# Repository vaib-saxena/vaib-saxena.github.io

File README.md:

## Welcome to my website "vaibsite.com"

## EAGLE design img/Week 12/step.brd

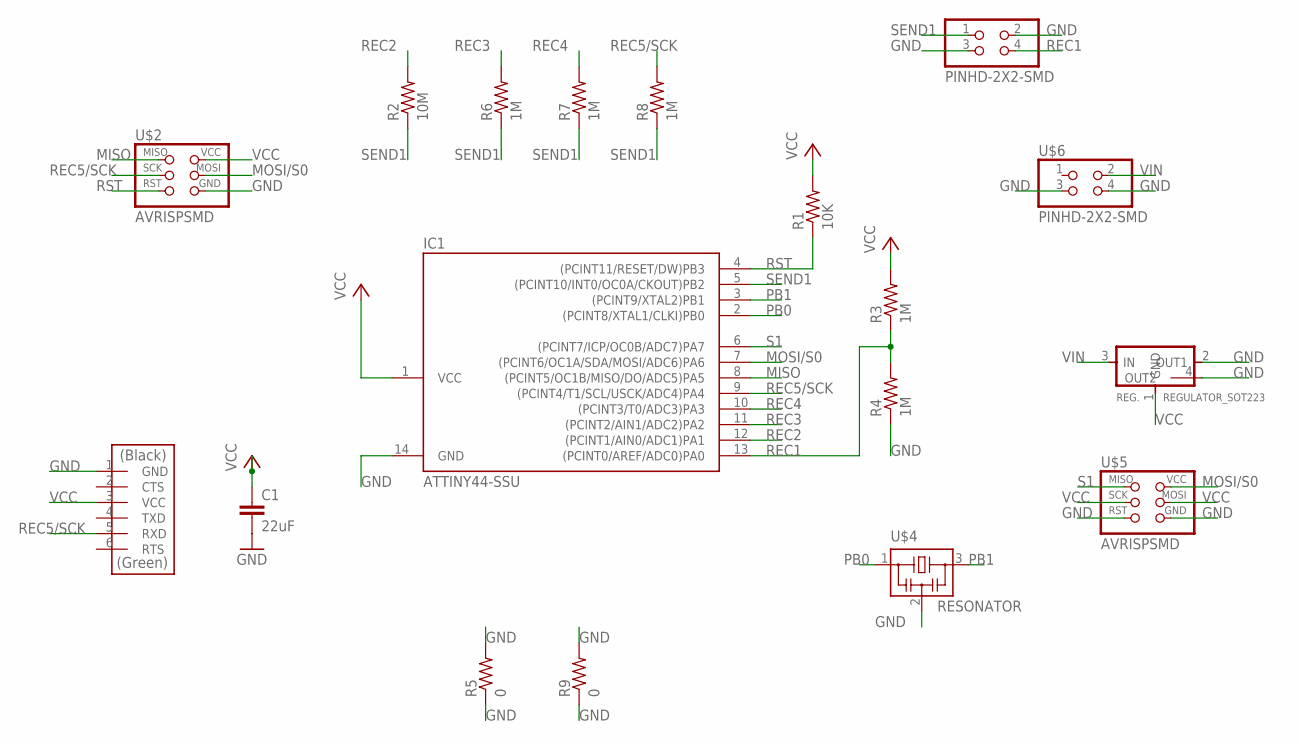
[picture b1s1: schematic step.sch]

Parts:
C1: 22uF; C1206
IC1: ATTINY44-SSU; SOIC14
R1: 10K; R1206FAB
R2: 10M; R1206FAB
R3, R4, R6, R7, R8: 1M; R1206FAB
R5, R9: 0; R1206FAB
REG.: REGULATOR_SOT223; SOT223
STEP/GND-SMD: PINHD-2X2-SMD; 2X02SMD
U$1: FTDI-SMD-HEADER; 1X06SMD
U$2, U$5: AVRISPSMD; 2X03SMD
U$4: RESONATOR; EFOBM
U$6: PINHD-2X2-SMD; 2X02SMD

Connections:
GND: C1.2, IC1.14 (GND), R4.1, R5.1, R5.2, R9.1, R9.2, REG..2 (OUT1), REG..4 (OUT2), STEP/GND-SMD.2, STEP/GND-SMD.3, U$1.1 (GND), U$2.6 (GND), U$4.2, U$5.5 (RST), U$5.6 (GND), U$6.3, U$6.4
MISO: IC1.8 ((PCINT5/OC1B/MISO/DO/ADC5)PA5), U$2.1 (MISO)
MOSI/S0: IC1.7 ((PCINT6/OC1A/SDA/MOSI/ADC6)PA6), U$2.4 (MOSI), U$5.2 (VCC)
PB0: IC1.2 ((PCINT8/XTAL1/CLKI)PB0), U$4.1
PB1: IC1.3 ((PCINT9/XTAL2)PB1), U$4.3
REC1: IC1.13 ((PCINT0/AREF/ADC0)PA0), R3.1, R4.2, STEP/GND-SMD.4
REC2: IC1.12 ((PCINT1/AIN0/ADC1)PA1), R2.2
REC3: IC1.11 ((PCINT2/AIN1/ADC2)PA2), R6.2
REC4: IC1.10 ((PCINT3/T0/ADC3)PA3), R7.2
REC5/SCK: IC1.9 ((PCINT4/T1/SCL/USCK/ADC4)PA4), R8.2, U$1.5 (RXD), U$2.3 (SCK)
RST: IC1.4 ((PCINT11/RESET/DW)PB3), R1.1, U$2.5 (RST)
S1: IC1.6 ((PCINT7/ICP/OC0B/ADC7)PA7), U$5.1 (MISO)
SEND1: IC1.5 ((PCINT10/INT0/OC0A/CKOUT)PB2), R2.1, R6.1, R7.1, R8.1, STEP/GND-SMD.1
VCC: C1.1, IC1.1 (VCC), R1.2, R3.2, REG..1 (GND), U$1.3 (VCC), U$2.2 (VCC), U$5.3 (SCK), U$5.4 (MOSI)
VIN: REG..3 (IN), U$6.2

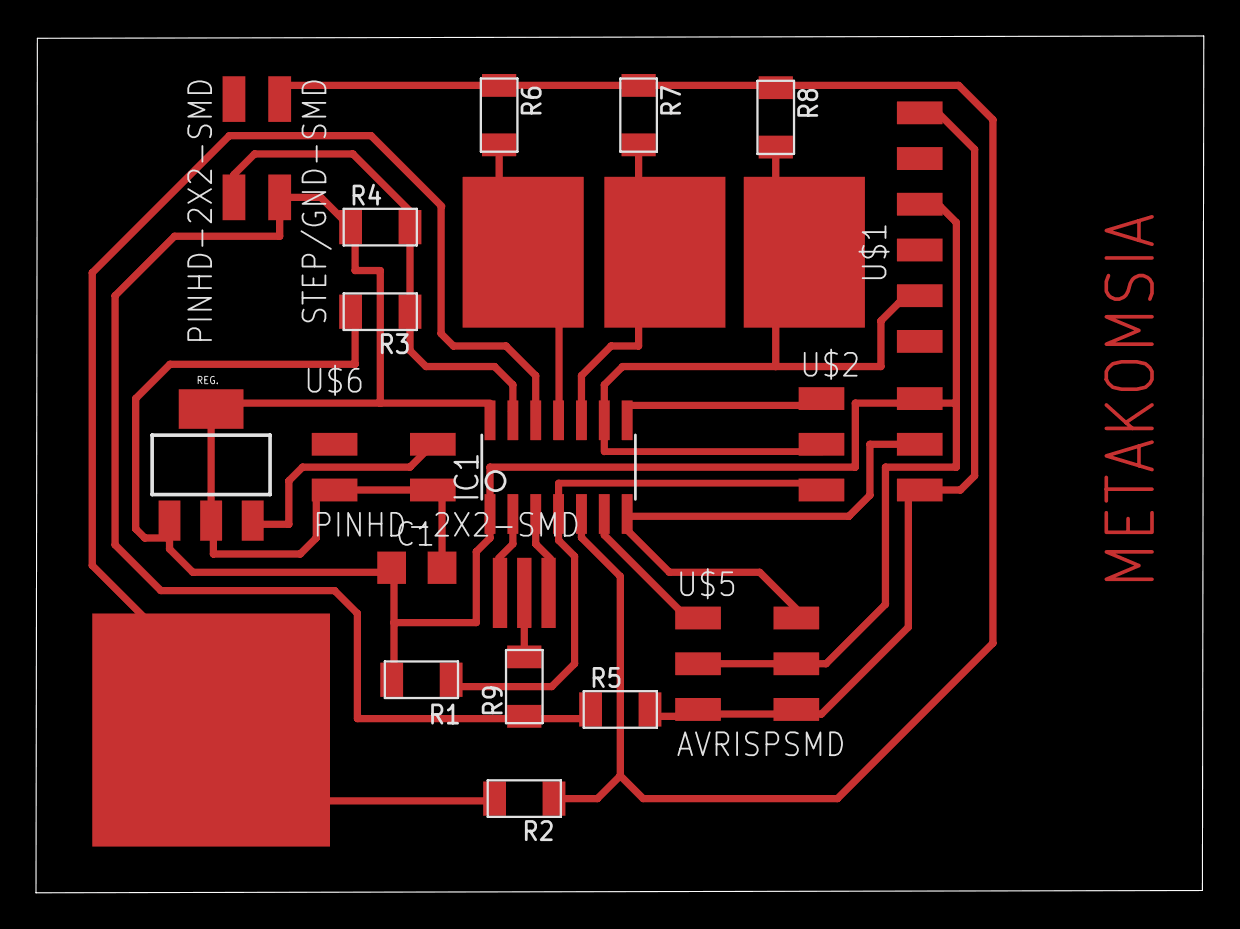
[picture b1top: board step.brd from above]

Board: 2 copper layers, 64.9 x 47.6 mm, 18 parts (0 on the bottom side), 15 nets.

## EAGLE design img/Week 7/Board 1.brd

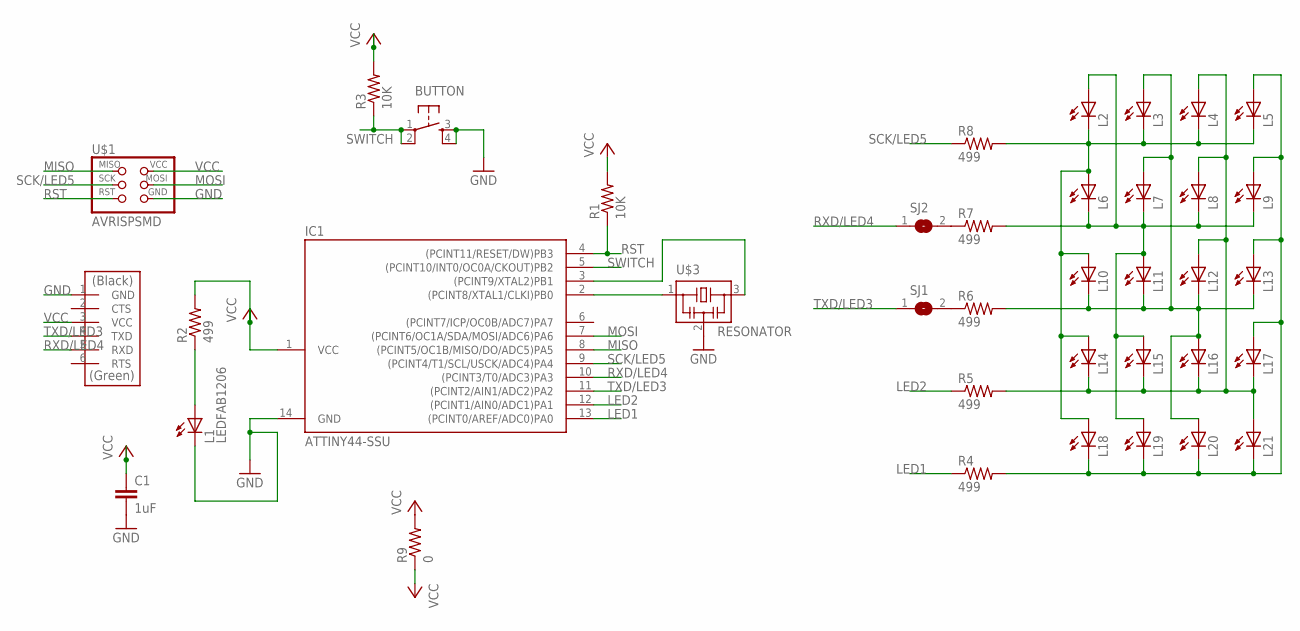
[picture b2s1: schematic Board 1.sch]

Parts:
BUTTON: 6MM_SWITCH6MM_SWITCH; 6MM_SWITCH
C1: 1uF; C1206
FTDIHEADER: FTDI-SMD-HEADER; 1X06SMD
IC1: ATTINY44-SSU; SOIC14
L1: LEDFAB1206; LED1206FAB
L2, L3, L4, L5, L6, L7, L8, L9, L10, L11, L12, L13, L14, L15, L16, L17, L18, L19, L20, L21: LED; LED1206
R1, R3: 10K; R1206FAB
R2, R4, R5, R6, R7, R8: 499; R1206FAB
R9: 0; R1206FAB
SJ1, SJ2: SJ
U$1: AVRISPSMD; 2X03SMD
U$3: RESONATOR; EFOBM

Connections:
A: L2.2 (C), L3.2 (C), L4.2 (C), L5.2 (C), L6.1 (A), L10.1 (A), L14.1 (A), L18.1 (A), R8.2
B: L2.1 (A), L6.2 (C), L7.2 (C), L8.2 (C), L9.2 (C), L11.1 (A), L15.1 (A), L19.1 (A), R7.2
C: L3.1 (A), L7.1 (A), L10.2 (C), L11.2 (C), L12.2 (C), L13.2 (C), L16.1 (A), L20.1 (A), R6.2
D: L4.1 (A), L8.1 (A), L12.1 (A), L14.2 (C), L15.2 (C), L16.2 (C), L17.2 (C), L21.1 (A), R5.2
E: L5.1 (A), L9.1 (A), L13.1 (A), L17.1 (A), L18.2 (C), L19.2 (C), L20.2 (C), L21.2 (C), R4.2
GND: BUTTON.3 (S), BUTTON.4 (S1), C1.2, FTDIHEADER.1 (GND), IC1.14 (GND), L1.2 (C), U$1.6 (GND), U$3.2
LED1: IC1.13 ((PCINT0/AREF/ADC0)PA0), R4.1
LED2: IC1.12 ((PCINT1/AIN0/ADC1)PA1), R5.1
MISO: IC1.8 ((PCINT5/OC1B/MISO/DO/ADC5)PA5), U$1.1 (MISO)
MOSI: IC1.7 ((PCINT6/OC1A/SDA/MOSI/ADC6)PA6), U$1.4 (MOSI)
unnamed: IC1.2 ((PCINT8/XTAL1/CLKI)PB0), U$3.1
unnamed: IC1.3 ((PCINT9/XTAL2)PB1), U$3.3
unnamed: L1.1 (A), R2.1
RST: IC1.4 ((PCINT11/RESET/DW)PB3), R1.1, U$1.5 (RST)
RXD/LED4: FTDIHEADER.5 (RXD), IC1.10 ((PCINT3/T0/ADC3)PA3), R7.1, SJ2.1, SJ2.2
SCK/LED5: IC1.9 ((PCINT4/T1/SCL/USCK/ADC4)PA4), R8.1, U$1.3 (SCK)
SWITCH: BUTTON.1, BUTTON.2 (P1), IC1.5 ((PCINT10/INT0/OC0A/CKOUT)PB2), R3.1
TXD/LED3: FTDIHEADER.4 (TXD), IC1.11 ((PCINT2/AIN1/ADC2)PA2), R6.1, SJ1.1, SJ1.2
VCC: C1.1, FTDIHEADER.3 (VCC), IC1.1 (VCC), R1.2, R2.2, R3.2, R9.1, R9.2, U$1.2 (VCC)

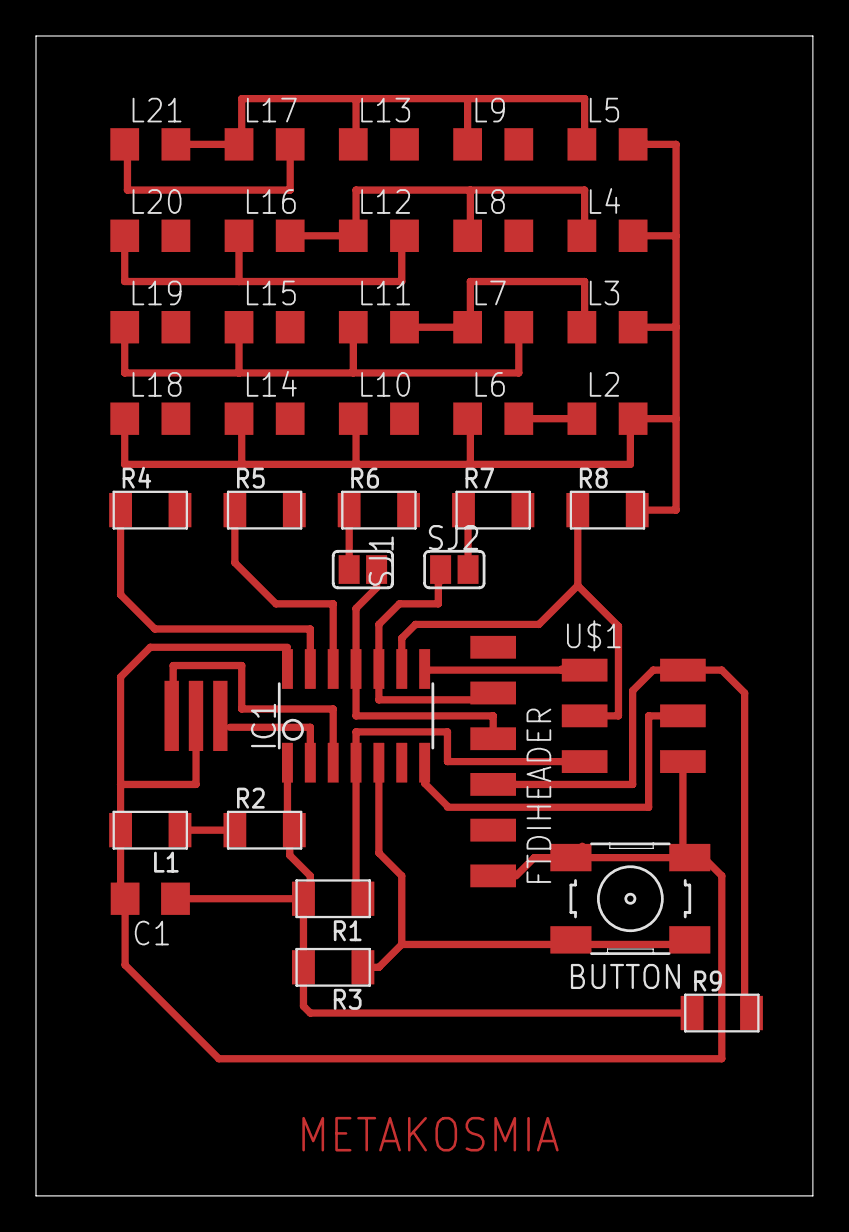
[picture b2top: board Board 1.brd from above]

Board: 2 copper layers, 43.2 x 64.4 mm, 38 parts (0 on the bottom side), 19 nets.

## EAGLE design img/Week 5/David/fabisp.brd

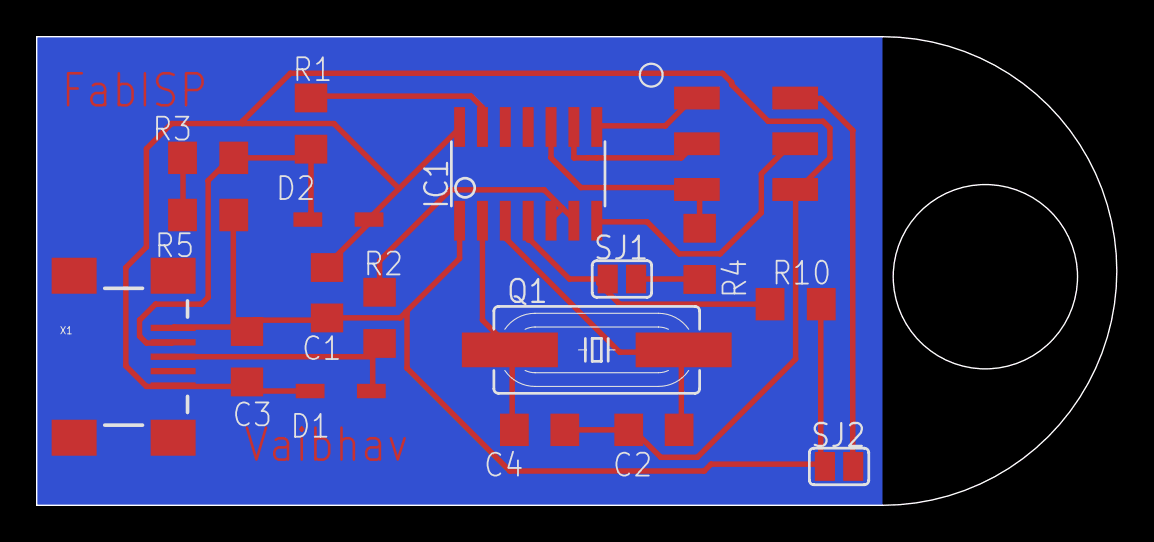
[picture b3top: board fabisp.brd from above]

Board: 2 copper layers, 60.0 x 26.0 mm, 18 parts (0 on the bottom side), 16 nets.

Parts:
C1: 0.1uF; C1206
C2, C4: 18pF; C1206
C3: 10uF; C1206
D1, D2: 3.3V; SOD123
IC1: ATTINY24/44/84-SSU; SOIC14
Q1: 12MHz; HC49UP
R1, R2: 49; R1206
R3: 1K; R1206
R4: 0; R1206
R5: 499; R1206
R10: 10K; R1206
SJ1: SJFAB
SJ2: SJFAB
U$1: 2X3HEADER; 2X3_SMD
X1: USB_MINIB

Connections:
D+: IC1.5, IC1.6, R2.2
D-: IC1.13, R1.2
GND: C1.2, C2.2, C3.2, C4.2, D1.ANODE, D2.ANODE, IC1.14, U$1.6, X1.GND
MISO: IC1.8, U$1.1
MOSI: IC1.7, U$1.4
unnamed: D2.CATHODE, R1.1, R3.1, X1.D-
unnamed: D1.CATHODE, R2.1, X1.D+
unnamed: R4.1, SJ1.2
unnamed: C4.1, IC1.2, Q1.1
unnamed: C2.1, IC1.3, Q1.2
unnamed: R3.2, R5.1
RESET: IC1.4, R10.1, SJ1.1
RST: IC1.10, R4.2, U$1.5
SCK: IC1.9, U$1.3
VCC: C1.1, C3.1, IC1.1, R5.2, R10.2, SJ2.1, X1.VBUS
VCC': SJ2.2, U$1.2

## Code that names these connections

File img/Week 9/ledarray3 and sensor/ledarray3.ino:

#include <SoftwareSerial.h>
#define RX PA3
#define TX PA2

SoftwareSerial mySerial(PA3, PA2); // RX, TX
#define A PA0
#define B PA1
#define C PA2
#define D PA3
#define E PA4
#define echoPin PA7
#define trigPin PA5

#define DELAY 500

int c2[5][4][2] =
  {
    { {B, A}, {C, A}, {D, A}, {E, A} },
    { {A, B}, {C, B}, {D, B}, {E, B} },
    { {A, C}, {B, C}, {D, C}, {E, C} },
    { {A, D}, {B, D}, {C, D}, {E, D} },
    { {A, E}, {B, E}, {C, E}, {D, E} }
  };

int times = 0;
int distance;
int duration;
void setup(){
  mySerial.begin(9600);
  pinMode( A, INPUT );
  pinMode( B, INPUT );
  pinMode( C, INPUT );
  pinMode( D, INPUT );
  pinMode( E, INPUT );
}


void light( int pins[2] ){
  pinMode( pins[0], OUTPUT );
  digitalWrite( pins[0], HIGH ); //making anode HIGH

  pinMode( pins[1], OUTPUT );
  digitalWrite( pins[1], LOW ); //making cathode LOW
}


void loop()
{
    digitalWrite(trigPin, LOW);
    delayMicroseconds(2);
    digitalWrite(trigPin, HIGH);
    delayMicroseconds(10);
    digitalWrite(trigPin, LOW);
    duration = pulseIn(echoPin, HIGH);
    distance = duration/58.2;
 
 if(distance<10)
 {
for(int i=0; i<5; i++)
{
  for(int j=0; j<4; j++)
  {
    light(c2[i][j]);
    }
    delay(100);
  } 
}
else
 {
for(int i=0; i<5; i++)
{
  for(int j=0; j<4; j++)
  {
    light(c2[i][j]);
    }
    delay(500);
  } 
}
}

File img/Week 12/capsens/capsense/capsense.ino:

#include <CapacitiveSensor.h>
#include <SoftwareSerial.h>


const int rx=PA6;
const int tx=PA7;

SoftwareSerial mySerial(rx, tx);
CapacitiveSensor   cs_2_1 = CapacitiveSensor(PB2,PA1);        // 10M resistor between pins 4 & 2, pin 2 is sensor pin, add a wire and or foil if desired. 

void setup()
{
   cs_2_1.set_CS_AutocaL_Millis(0xFFFFFFFF);     // turn off autocalibrate on channel 1 - just as an example
    mySerial.begin(9600);        //  Begins Serial Communication at 9600baud.
}

void loop()
{
 
    long start = millis();
    long total1 =  cs_2_1.capacitiveSensor(1000);

    mySerial.print(millis() - start);        // check on performance in milliseconds
    mySerial.print("\t");                    // tab character for debug window spacing
    mySerial.println(total1);                  // Sends the value of total1 to the Serial window of the computer
    delay(10);

}
  

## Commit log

2019-06-15 commit 0
2019-06-15 commit 1
2019-06-20 commit 2
2019-06-20 commit 3
2019-06-20 commited
2019-06-22 commit 4
2020-01-09 new22
2020-01-10 nono
2020-01-13 archnet
2020-01-14 width
2020-01-14 maxwidth
2020-01-14 width2
2020-01-14 newcss
2020-01-14 try1
2020-01-14 tryy
2020-01-14 retry
2020-01-14 centerrrr
2020-01-14 naya
2020-01-14 ione
2020-01-14 niuol
2020-01-14 roko
2020-01-16 update2
2020-01-18 bcg1
2020-01-19 bcg3
2020-01-20 bcgdig
2020-01-20 bbddgg
2020-01-20 remove ml
2020-01-20 check
2020-01-20 disclaimer
2020-01-20 correcton
2020-01-21 rlupdate
2020-01-21 rl_new
2020-01-22 boston
2020-01-22 new changes
2020-01-23 salted
2020-01-23 saltfi
2020-01-23 under
2020-01-23 blank
2020-01-25 soft
2020-01-27 mahi
2020-01-27 tracker
2020-04-22 njmk
2022-11-27 update CNAME
2024-06-14 Create CNAME
